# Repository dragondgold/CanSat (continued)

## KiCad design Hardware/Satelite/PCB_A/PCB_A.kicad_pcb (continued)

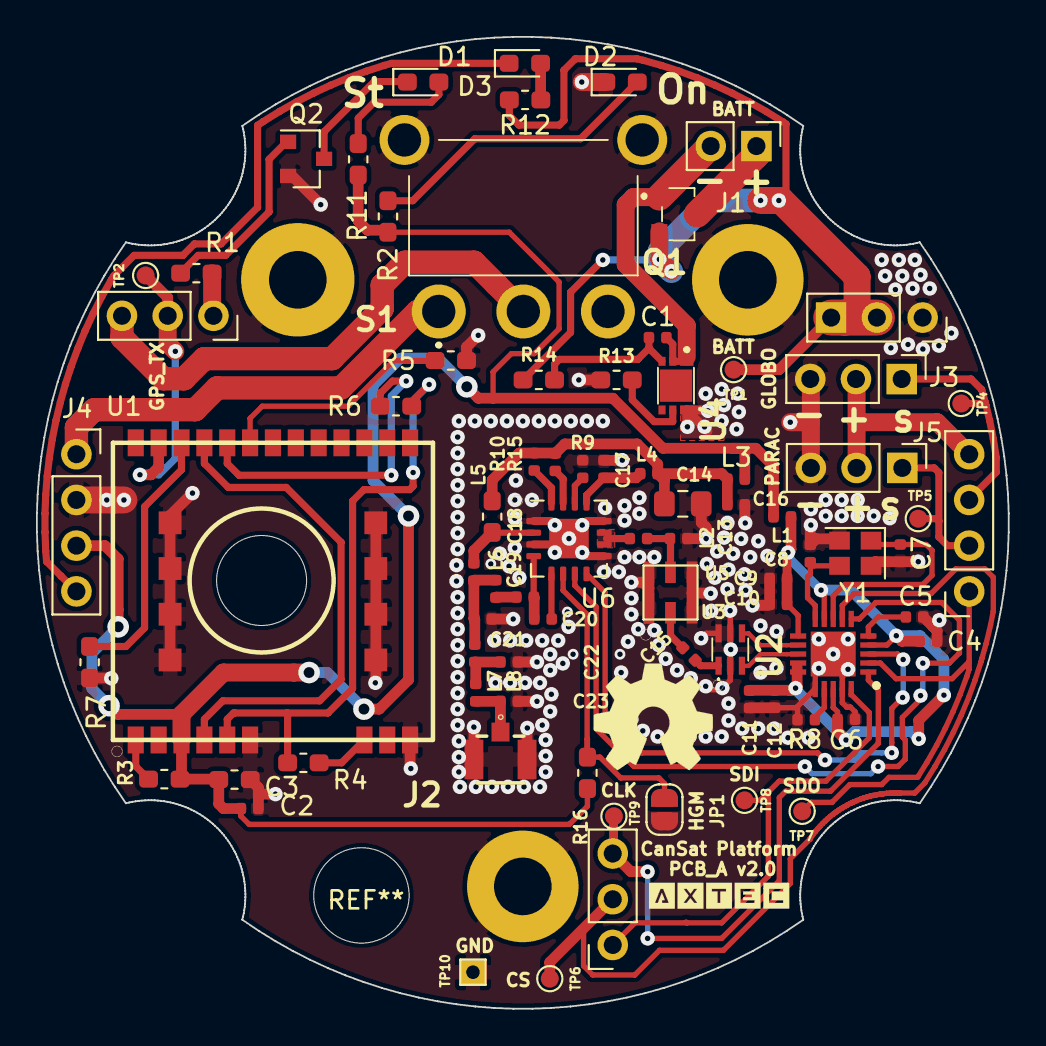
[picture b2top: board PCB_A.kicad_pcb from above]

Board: 2 copper layers, 54.0 x 54.0 mm, 79 parts (0 on the bottom side), 57 nets.

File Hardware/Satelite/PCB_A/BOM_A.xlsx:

Qty | Reference(s) | Value | Footprint | Manufacturer Part Number
9 | C1, C2, C4, C5, C6, C9, C10, C11, C12 | 100nF | Capacitor_SMD:C_0402_1005Metric | GCM155R71C104KA55D
1 | C3 | 1uF | Capacitor_SMD:C_0603_1608Metric_Pad1.05x0.95mm_HandSolder | LMK107B7105MA-T
4 | C7, C8, C16, C17 | 15pF | Capacitor_SMD:C_0402_1005Metric | C0402C150J5GACTU
1 | C13 | 0.8pF | Capacitor_SMD:C_0402_1005Metric | GRM1555C2AR80BA01D
1 | C14 | 10uF | Capacitor_SMD:C_0805_2012Metric_Pad1.15x1.40mm_HandSolder | C2012X7R1A106M125AC
1 | C15 | 100pF | Capacitor_SMD:C_0402_1005Metric | 885012005046
1 | C18 | 47pF | Capacitor_SMD:C_0402_1005Metric | GCM1555C1H470JA16J
2 | C19, C20 | 12pF | Capacitor_SMD:C_0402_1005Metric | GRM1555C1H120GA01D
1 | C21 | 3.3pF | Capacitor_SMD:C_0402_1005Metric | GJM1555C1H3R3DB01D
1 | C22 | 7.5pF | Capacitor_SMD:C_0402_1005Metric | GCM1555C1H7R5DA16D
1 | C23 | n.a | Capacitor_SMD:C_0402_1005Metric
1 | D1 | Rojo | LED_SMD:LED_0603_1608Metric_Pad1.05x0.95mm_HandSolder | 150060RS75000
2 | D2, D3 | Verde | LED_SMD:LED_0603_1608Metric_Pad1.05x0.95mm_HandSolder | 150060VS75000
1 | J1 | BaterÃ­a LiPo (Soldada) | Connector_PinHeader_2.54mm:PinHeader_1x02_P2.54mm_Vertical
1 | J2 | CONUFL001-SMD | SamacSys_Parts:CONUFL001-SMD | CONUFL001-SMD
1 | J3 | Servo Globo | Connector_PinHeader_2.54mm:PinHeader_1x03_P2.54mm_Vertical
3 | J4 | Conector_PCB_A-B | AXTEC:Conector_PCB_A-B | 22-28-5034
2 | J4 | Conector_PCB_A-B | AXTEC:Conector_PCB_A-B | 22-28-4041
1 | J5 | Servo ParacaÃ­das | Connector_PinHeader_2.54mm:PinHeader_1x03_P2.54mm_Vertical
1 | JP1 | Jumper | Jumper:SolderJumper-2_P1.3mm_Open_RoundedPad1.0x1.5mm
1 | L1 | Bead | Inductor_SMD:L_0402_1005Metric | BLM15HG102SN1D
2 | L2, L3 | 10nH | Inductor_SMD:L_0402_1005Metric | LQG15HN10NH02D
1 | L4 | 1.5nH | Inductor_SMD:L_0402_1005Metric | LQG15HS1N5S02D
1 | L5 | 22nH | Inductor_SMD:L_0603_1608Metric_Pad1.05x0.95mm_HandSolder | LQW18AN22NJ10D
1 | L6 | 7.5nH | Inductor_SMD:L_0402_1005Metric | LQW15AN7N5G00D
1 | L7 | 2.9nH | Inductor_SMD:L_0402_1005Metric | LQW15AN2N9B00D
1 | L8 | 9.1nH | Inductor_SMD:L_0402_1005Metric | LQW15AN9N1G00D
3 | M1, M2, M3 | Spacer | AXTEC:Empty_Footprint | R30-3011002
1 | MH1 | MH_CanSat | AXTEC:MH_CanSat
1 | Q1 | SSM3J338R,LF | SamacSys_Parts:SSM3J332RLFT | SSM3J338R,LF
1 | Q2 | BC817 | Package_TO_SOT_SMD:SOT-23 | BC817-16LT1G
4 | R1, R2, R11, R12 | 1k | Resistor_SMD:R_0603_1608Metric_Pad1.05x0.95mm_HandSolder | RC0603JR-071KL
5 | R3, R4, R5, R6, R7 | 10k | Resistor_SMD:R_0603_1608Metric_Pad1.05x0.95mm_HandSolder | RC0603JR-0710KL
1 | R8 | 56k | Resistor_SMD:R_0402_1005Metric | RC0402FR-0756KL
1 | R9 | 3.3k | Resistor_SMD:R_0402_1005Metric | RC0402FR-073K3L
1 | R10 | 10R | Resistor_SMD:R_0402_1005Metric | RC0402FR-0710RL
1 | R13 | 2.7k | Resistor_SMD:R_0603_1608Metric_Pad1.05x0.95mm_HandSolder | RC0603FR-072K7L
1 | R14 | 330 | Resistor_SMD:R_0603_1608Metric_Pad1.05x0.95mm_HandSolder | RC0603FR-07330RL
1 | R15 | 47R | Resistor_SMD:R_0402_1005Metric | RC0402FR-0747RL
1 | R16 | 10K | Resistor_SMD:R_0603_1608Metric_Pad1.05x0.95mm_HandSolder | RC0603JR-0710KL
1 | S1 | 500SSP1S1M6QEA | SamacSys_Parts:500SSP1S1M6QEA | 500SSP1S1M6QEA
1 | U1 | A2235-H | AXTEC:A2235-H | A2235-H
1 | U2 | CC1101RGP | SamacSys_Parts:QFN50P400X400X100-21N-D | CC1101RGP
1 | U3 | 0915BM15A0001E | SamacSys_Parts:0915BM15A0001E | 0915BM15A0001E
1 | U4 | AP9211SA-AF-HAC-7 | SamacSys_Parts:AP9211SAACHAC7 | AP9211SA-AF-HAC-7
1 | U5 | B39921B3588U410 | AXTEC:B39921B3588U410 | B39921B3588U410
1 | U6 | CC1190 | Package_DFN_QFN:Texas_S-PVQFN-N16_EP2.7x2.7mm | CC1190RGVR
1 | Y1 | 26 MHz | Crystal:Crystal_SMD_2520-4Pin_2.5x2.0mm | FA-20H 26.0000MF12V-W
1 |  | Antena 915 MHz |  | W3312B0100

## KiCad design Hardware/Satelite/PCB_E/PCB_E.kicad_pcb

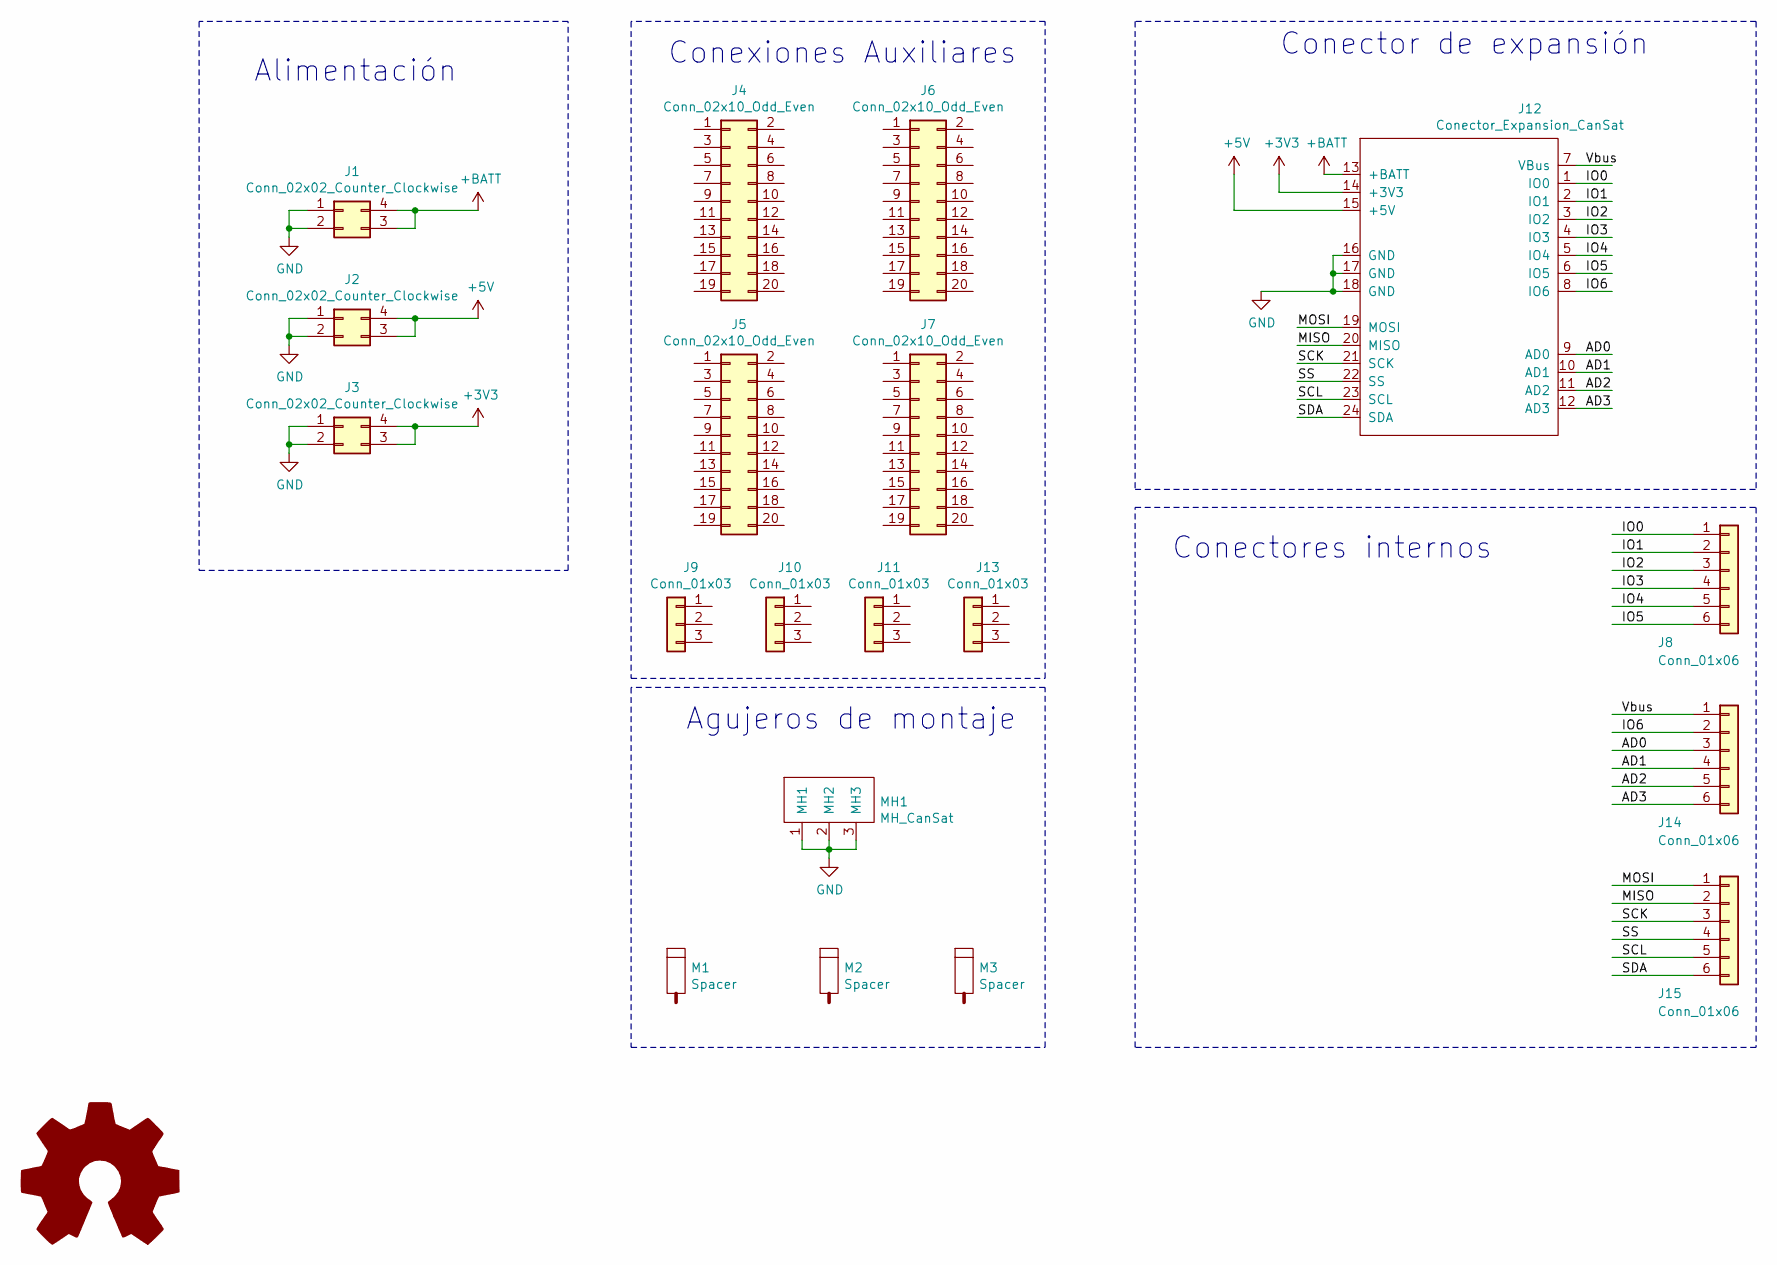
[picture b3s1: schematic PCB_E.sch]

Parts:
J1, J2, J3: Conn_02x02_Counter_Clockwise; PinSocket_2x02_P2.54mm_Vertical
J4, J5, J6, J7: Conn_02x10_Odd_Even; PinSocket_2x10_P2.54mm_Vertical
J8, J14, J15: Conn_01x06; PinHeader_1x06_P2.54mm_Vertical
J9, J10, J11, J13: Conn_01x03; PinHeader_1x03_P2.54mm_Vertical
J12: Conector_Expansion_CanSat
M1, M2, M3: Spacer; Empty_Footprint; Manufacturer Part Number R30-3011202
MH1: MH_CanSat

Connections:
+3V3: J3.3, J3.4, J12.14 (+3V3)
+5V: J2.3, J2.4, J12.15 (+5V)
+BATT: J1.3, J1.4, J12.13 (+BATT)
/AD0: J12.9 (AD0), J14.3
/AD1: J12.10 (AD1), J14.4
/AD2: J12.11 (AD2), J14.5
/AD3: J12.12 (AD3), J14.6
/IO0: J8.1, J12.1 (IO0)
/IO1: J8.2, J12.2 (IO1)
/IO2: J8.3, J12.3 (IO2)
/IO3: J8.4, J12.4 (IO3)
/IO4: J8.5, J12.5 (IO4)
/IO5: J8.6, J12.6 (IO5)
/IO6: J12.8 (IO6), J14.2
/MISO: J12.20 (MISO), J15.2
/MOSI: J12.19 (MOSI), J15.1
/SCK: J12.21 (SCK), J15.3
/SCL: J12.23 (SCL), J15.5
/SDA: J12.24 (SDA), J15.6
/SS: J12.22 (SS), J15.4
/Vbus: J12.7 (VBus), J14.1
GND: J1.1, J1.2, J2.1, J2.2, J3.1, J3.2, J12.16 (GND), J12.17 (GND), J12.18 (GND), MH1.1 (MH1), MH1.2 (MH2), MH1.3 (MH3)

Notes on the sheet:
Conexiones Auxiliares
Alimentación
Conectores internos
Conector de expansión
Agujeros de montaje

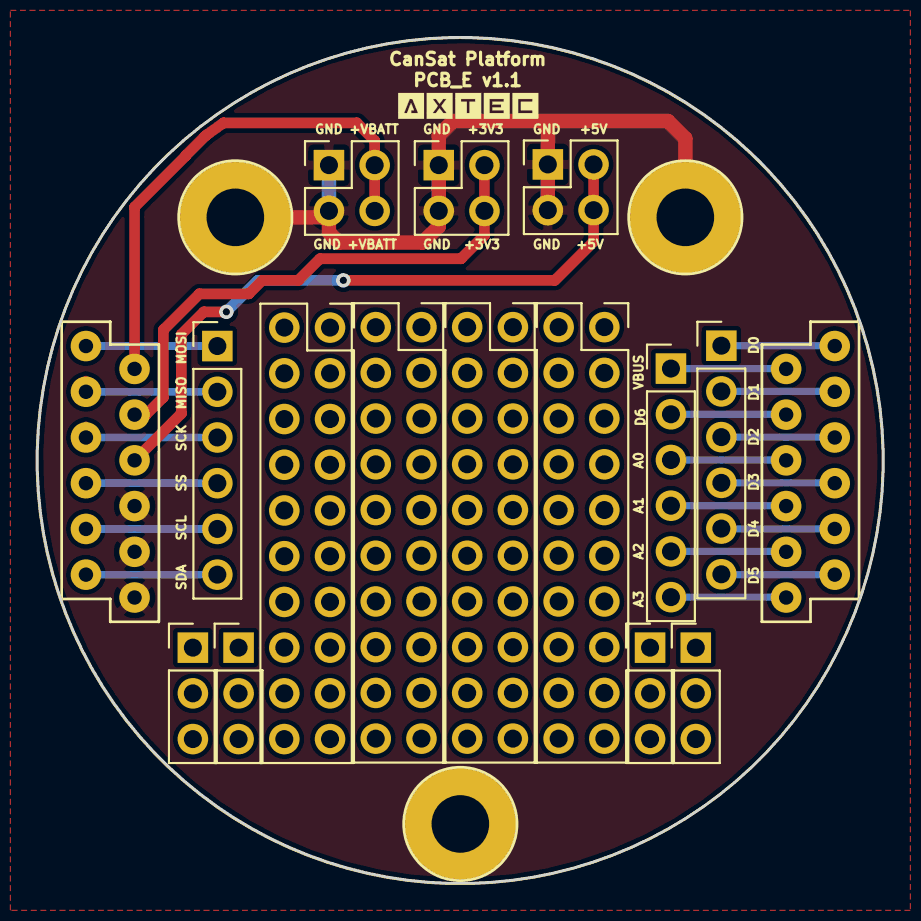
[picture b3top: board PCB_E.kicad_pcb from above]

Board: 2 copper layers, 47.0 x 47.0 mm, 19 parts (0 on the bottom side), 22 nets.

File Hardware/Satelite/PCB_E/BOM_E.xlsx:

Qty | Reference(s) | Value | Footprint | Manufacturer Part Number
3 | J1, J2, J3 | Conn_02x02_Counter_Clockwise | Connector_PinSocket_2.54mm:PinSocket_2x02_P2.54mm_Vertical
4 | J4, J5, J6, J7 | Conn_02x10_Odd_Even | Connector_PinSocket_2.54mm:PinSocket_2x10_P2.54mm_Vertical
3 | J8, J14, J15 | Conn_01x06 | Connector_PinHeader_2.54mm:PinHeader_1x06_P2.54mm_Vertical
4 | J9, J10, J11, J13 | Conn_01x03 | Connector_PinHeader_2.54mm:PinHeader_1x03_P2.54mm_Vertical
4 | J12 | Conector_Expansion_CanSat | AXTEC:Conector_Expansion_CanSat | SSQ-106-03-T-S
3 | M1, M2, M3 | Spacer | AXTEC:Empty_Footprint | R30-3011202
1 | MH1 | MH_CanSat | AXTEC:MH_CanSat

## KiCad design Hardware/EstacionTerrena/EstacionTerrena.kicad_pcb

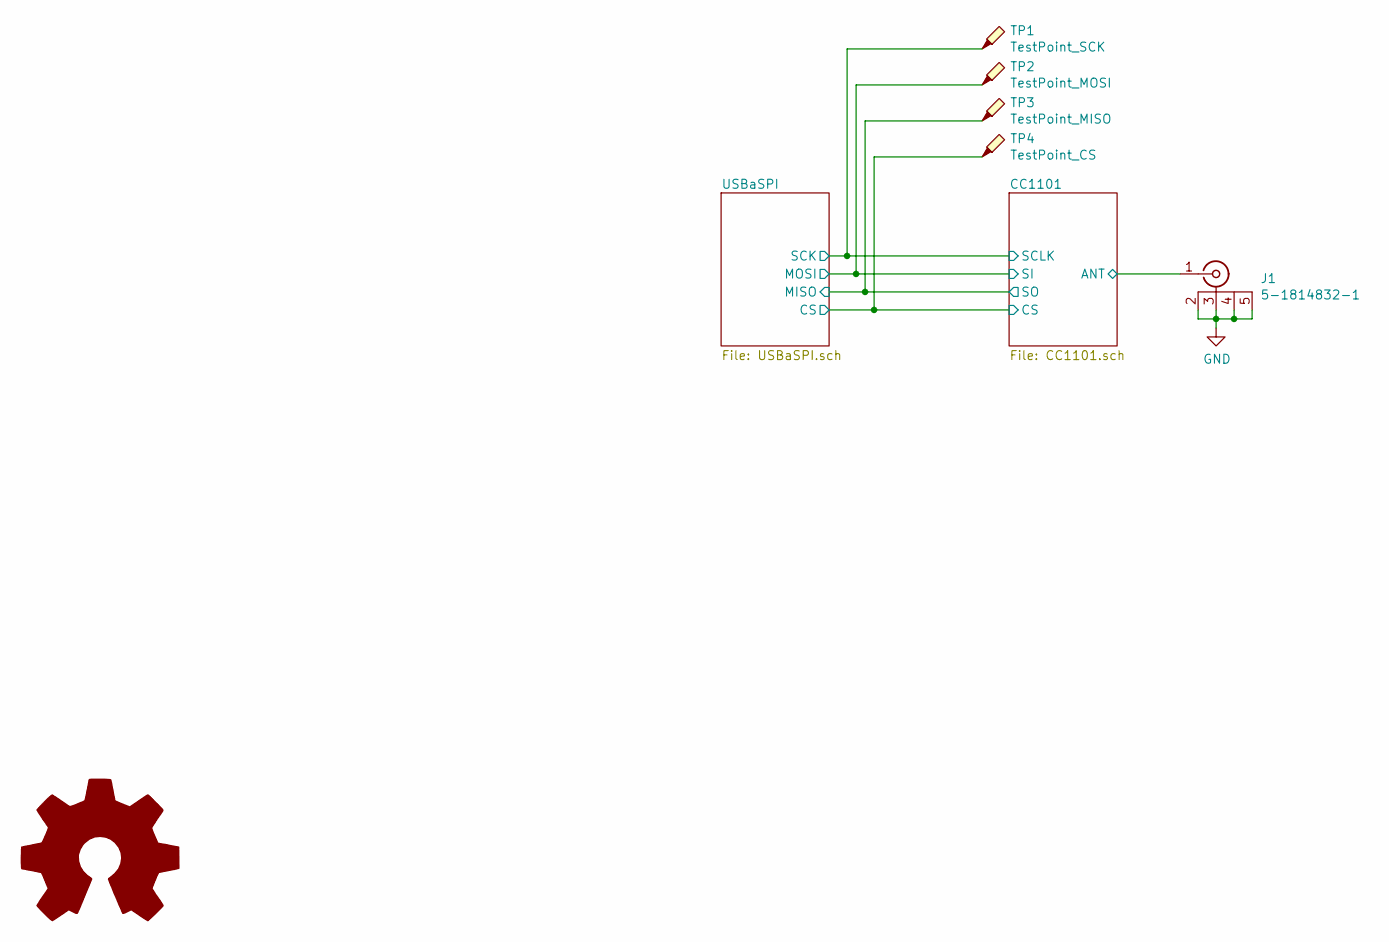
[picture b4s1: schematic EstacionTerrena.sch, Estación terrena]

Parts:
J1: 5-1814832-1; Manufacturer Part Number 5-1814832-1
TP1: TestPoint_SCK; TestPoint_Pad_D1.0mm
TP2: TestPoint_MOSI; TestPoint_Pad_D1.0mm
TP3: TestPoint_MISO; TestPoint_Pad_D1.0mm
TP4: TestPoint_CS; TestPoint_Pad_D1.0mm

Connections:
/CC1101/ANT: J1.1; also elsewhere on the board
/CC1101/CS: TP4.1; also elsewhere on the board
/USBaSPI/MISO: TP3.1; also elsewhere on the board
/USBaSPI/MOSI: TP2.1; also elsewhere on the board
/USBaSPI/SCK: TP1.1; also elsewhere on the board
GND: J1.2, J1.3, J1.4, J1.5; also elsewhere on the board

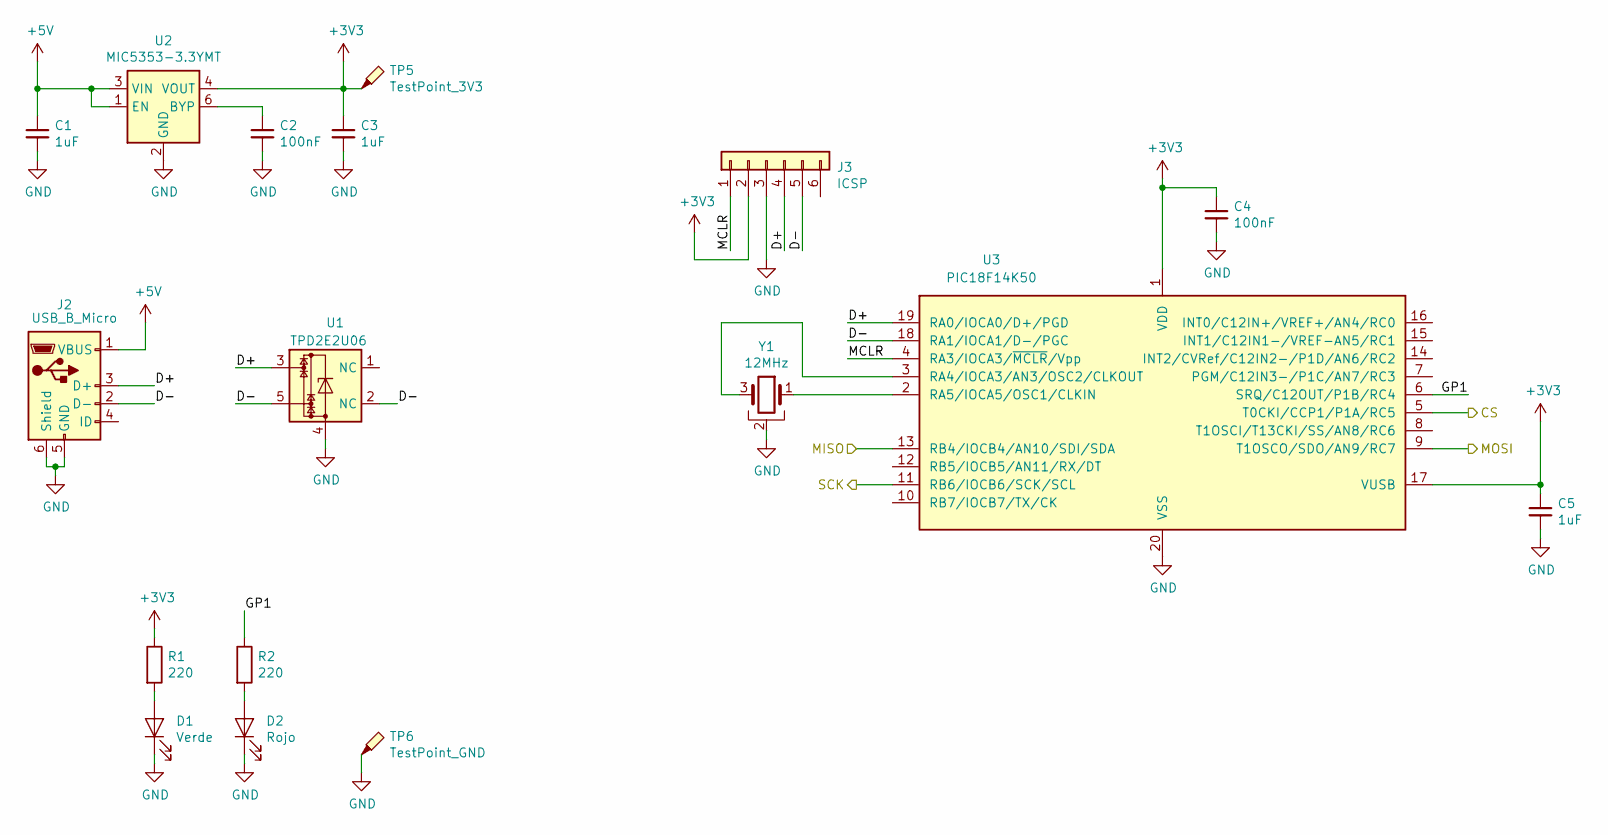
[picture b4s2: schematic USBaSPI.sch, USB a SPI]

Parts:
C1, C3, C5: 1uF; C_0603_1608Metric; Voltage 10V; Manufacturer Part Number LMK107B7105MA-T
C2, C4: 100nF; C_0603_1608Metric; Voltage 16V; Manufacturer Part Number EMK107B7104KAHT
D1: Verde; LED_0603_1608Metric; Manufacturer Part Number 150060VS75000
D2: Rojo; LED_0603_1608Metric; Manufacturer Part Number 150060RS75000
J2: USB_B_Micro; USB_Micro-B_Molex_47346-0001; Manufacturer Part Number 47346-1001
J3: ICSP; PinHeader_1x06_P2.54mm_Vertical
R1, R2: 220; R_0603_1608Metric_Pad1.05x0.95mm_HandSolder; Manufacturer Part Number RC0603JR-13220RL
TP5: TestPoint_3V3; TestPoint_Pad_D1.0mm
TP6: TestPoint_GND; TestPoint_THTPad_1.0x1.0mm_Drill0.5mm
U1: TPD2E2U06; SOT-553; Manufacturer Part Number TPD2E2U06DRLR
U2: MIC5353-3.3YMT; MLF-6-1EP_1.6x1.6mm_P0.5mm_EP0.5x1.26mm; Manufacturer Part Number MIC5353-3.3YMT-TR
U3: PIC18F14K50; SSOP-20_5.3x7.2mm_P0.65mm; Manufacturer Part Number PIC18F14K50-I/SS
Y1: 12MHz; Resonator_SMD_muRata_CSTxExxV-3Pin_3.0x1.1mm; Manufacturer Part Number CSTNE12M0GH5L000R0

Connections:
+3V3: C3.1, C4.1, C5.1, J3.2, R1.1, TP5.1, U2.4 (VOUT), U3.1 (VDD), U3.17 (VUSB); also elsewhere on the board
+5V: C1.1, J2.1 (VBUS), U2.1 (EN), U2.3 (VIN)
/CC1101/CS: U3.5 (T0CKI/CCP1/P1A/RC5); also elsewhere on the board
/USBaSPI/D+: J2.3 (D+), J3.4, U1.3, U3.19 (RA0/IOCA0/D+/PGD)
/USBaSPI/D-: J2.2 (D-), J3.5, U1.2 (NC), U1.5, U3.18 (RA1/IOCA1/D-/PGC)
/USBaSPI/GP1: R2.1, U3.6 (SRQ/C12OUT/P1B/RC4)
/USBaSPI/MCLR: J3.1, U3.4 (RA3/IOCA3/~MCLR~/Vpp)
/USBaSPI/MISO: U3.13 (RB4/IOCB4/AN10/SDI/SDA); also elsewhere on the board
/USBaSPI/MOSI: U3.9 (T1OSCO/SDO/AN9/RC7); also elsewhere on the board
/USBaSPI/SCK: U3.11 (RB6/IOCB6/SCK/SCL); also elsewhere on the board
GND: C1.2, C2.2, C3.2, C4.2, C5.2, D1.1 (K), D2.1 (K), J2.5 (GND), J2.6 (Shield), J3.3, TP6.1, U1.4, U2.2 (GND), U2.7 (GND), U3.20 (VSS), Y1.2; also elsewhere on the board
unnamed: C2.1, U2.6 (BYP)
unnamed: D1.2 (A), R1.2
unnamed: D2.2 (A), R2.2
unnamed: U3.2 (RA5/IOCA5/OSC1/CLKIN), Y1.1
unnamed: U3.3 (RA4/IOCA3/AN3/OSC2/CLKOUT), Y1.3

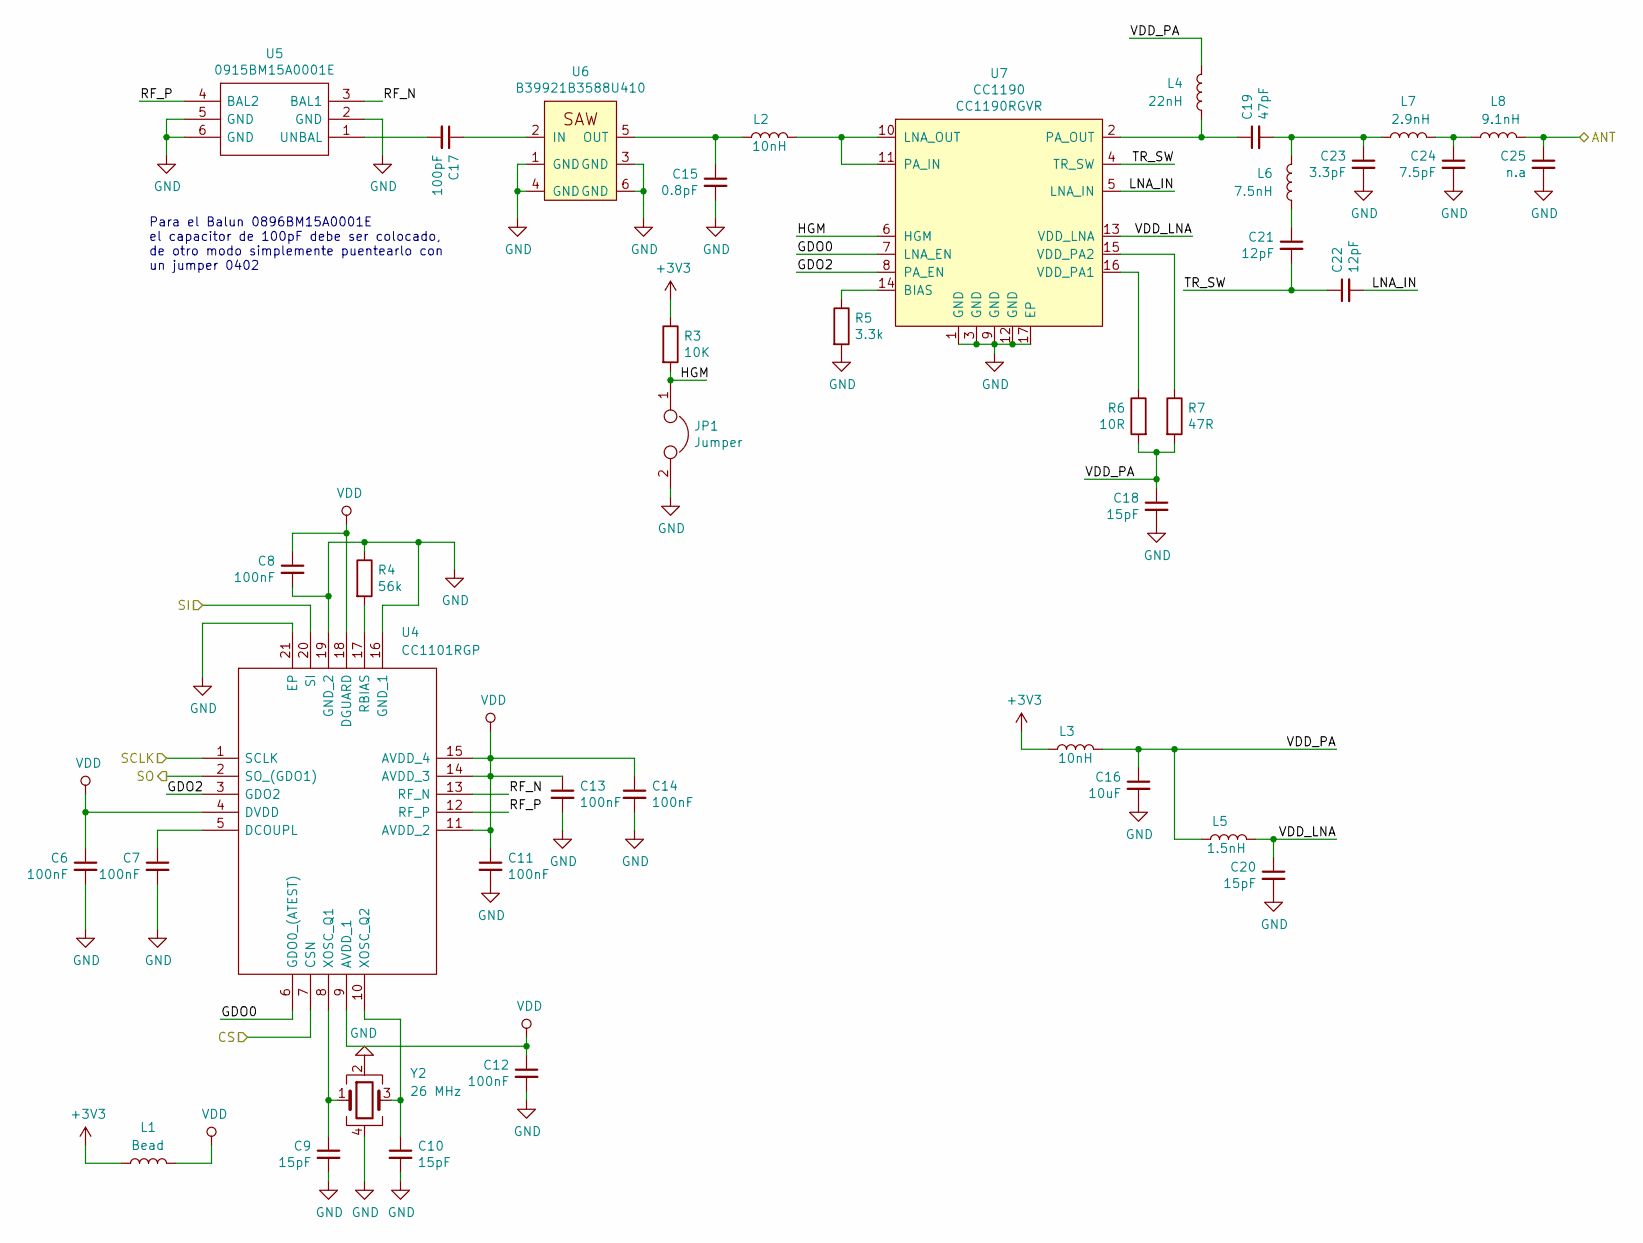
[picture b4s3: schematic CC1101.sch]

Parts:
C6, C7, C8, C11, C12, C13, C14: 100nF; C_0402_1005Metric; Voltage 16V; Manufacturer Part Number GCM155R71C104KA55D
C9, C10: 15pF; C_0402_1005Metric; Voltage 10V; Manufacturer Part Number C0402C150J5GACTU
C15: 0.8pF; C_0402_1005Metric; Manufacturer Part Number GRM1555C2AR80BA01D
C16: 10uF; C_0805_2012Metric_Pad1.15x1.40mm_HandSolder; Manufacturer Part Number C2012X7R1A106M125AC
C17: 100pF; C_0402_1005Metric; Voltage 25V; Manufacturer Part Number 885012005046
C18, C20: 15pF; C_0402_1005Metric; Manufacturer Part Number CC0402JRNPO9BN150
C19: 47pF; C_0402_1005Metric; Manufacturer Part Number GCM1555C1H470JA16J
C21, C22: 12pF; C_0402_1005Metric; Manufacturer Part Number GRM1555C1H120GA01D
C23: 3.3pF; C_0402_1005Metric; Manufacturer Part Number GJM1555C1H3R3DB01D
C24: 7.5pF; C_0402_1005Metric; Manufacturer Part Number GCM1555C1H7R5DA16D
C25: n.a; C_0402_1005Metric
JP1: Jumper; SolderJumper-2_P1.3mm_Open_RoundedPad1.0x1.5mm
L1: Bead; L_0402_1005Metric; Manufacturer Part Number BLM15HG102SN1D
L2, L3: 10nH; L_0402_1005Metric; Manufacturer Part Number LQG15HN10NH02D
L4: 22nH; L_0603_1608Metric_Pad1.05x0.95mm_HandSolder; Manufacturer Part Number LQW18AN22NJ10D
L5: 1.5nH; L_0402_1005Metric; Manufacturer Part Number LQG15HS1N5S02D
L6: 7.5nH; L_0402_1005Metric; Manufacturer Part Number LQW15AN7N5G00D
L7: 2.9nH; L_0402_1005Metric; Manufacturer Part Number LQW15AN2N9B00D
L8: 9.1nH; L_0402_1005Metric; Manufacturer Part Number LQW15AN9N1G00D
R3: 10K; R_0603_1608Metric_Pad1.05x0.95mm_HandSolder; Manufacturer Part Number RC0603JR-0710KL
R4: 56k; R_0402_1005Metric; Manufacturer Part Number RC0402FR-0756KL
R5: 3.3k; R_0402_1005Metric; Manufacturer Part Number RC0402FR-073K3L
R6: 10R; R_0402_1005Metric; Manufacturer Part Number RC0402FR-0710RL
R7: 47R; R_0402_1005Metric; Manufacturer Part Number RC0402FR-0747RL
U4: CC1101RGP; QFN-20-1EP_4x4mm_P0.5mm_EP2.5x2.5mm; Manufacturer Part Number CC1101RGP
U5: 0915BM15A0001E; Manufacturer Part Number 0915BM15A0001E
U6: B39921B3588U410; Manufacturer Part Number B39921B3588U410
U7: CC1190; Texas_S-PVQFN-N16_EP2.7x2.7mm; Manufactuer Part Number CC1190RGVR
Y2: 26 MHz; Crystal_SMD_2520-4Pin_2.5x2.0mm; Manufacturer Part Number FA-20H 26.0000MF12V-W

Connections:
+3V3: L1.2, L3.1, R3.1; also elsewhere on the board
/CC1101/ANT: C25.1, L8.1; also elsewhere on the board
/CC1101/CS: U4.7 (CSN); also elsewhere on the board
/CC1101/GDO0: U4.6 (GDO0_(ATEST)), U7.7 (LNA_EN)
/CC1101/GDO2: U4.3 (GDO2), U7.8 (PA_EN)
/CC1101/HGM: JP1.1, R3.2, U7.6 (HGM)
/CC1101/LNA_IN: C22.2, U7.5 (LNA_IN)
/CC1101/RF_N: U4.13 (RF_N), U5.3 (BAL1)
/CC1101/RF_P: U4.12 (RF_P), U5.4 (BAL2)
/CC1101/TR_SW: C21.2, C22.1, U7.4 (TR_SW)
/CC1101/VDD_LNA: C20.1, L5.2, U7.13 (VDD_LNA)
/CC1101/VDD_PA: C16.1, C18.1, L3.2, L4.1, L5.1, R6.2, R7.2
/USBaSPI/MISO: U4.2 (SO_(GDO1)); also elsewhere on the board
/USBaSPI/MOSI: U4.20 (SI); also elsewhere on the board
/USBaSPI/SCK: U4.1 (SCLK); also elsewhere on the board
GND: C6.2, C7.2, C8.2, C9.2, C10.2, C11.2, C12.2, C13.2, C14.2, C15.2, C16.2, C18.2, C20.2, C23.2, C24.2, C25.2, JP1.2, R4.1, R5.2, U4.16 (GND_1), U4.19 (GND_2), U4.21 (EP), U5.2 (GND), U5.5 (GND), U5.6 (GND), U6.1 (GND), U6.3 (GND), U6.4 (GND), U6.6 (GND), U7.1 (GND), U7.3 (GND), U7.9 (GND), U7.12 (GND), U7.17 (EP), Y2.2, Y2.4; also elsewhere on the board
unnamed: C7.1, U4.5 (DCOUPL)
unnamed: C9.1, U4.8 (XOSC_Q1), Y2.1
unnamed: C10.1, U4.10 (XOSC_Q2), Y2.3
unnamed: C15.1, L2.1, U6.5 (OUT)
unnamed: C17.1, U6.2 (IN)
unnamed: C17.2, U5.1 (UNBAL)
unnamed: C19.1, L4.2, U7.2 (PA_OUT)
unnamed: C19.2, C23.1, L6.1, L7.2
unnamed: C21.1, L6.2
unnamed: C24.1, L7.1, L8.2
unnamed: L2.2, U7.10 (LNA_OUT), U7.11 (PA_IN)
unnamed: R4.2, U4.17 (RBIAS)
unnamed: R5.1, U7.14 (BIAS)
unnamed: R6.1, U7.16 (VDD_PA1)
unnamed: R7.1, U7.15 (VDD_PA2)
VDD: C6.1, C8.1, C11.1, C12.1, C13.1, C14.1, L1.1, U4.4 (DVDD), U4.9 (AVDD_1), U4.11 (AVDD_2), U4.14 (AVDD_3), U4.15 (AVDD_4), U4.18 (DGUARD)

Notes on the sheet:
Para el Balun 0896BM15A0001E el capacitor de 100pF debe ser colocado, de otro modo simplemente puentearlo con un jumper 0402

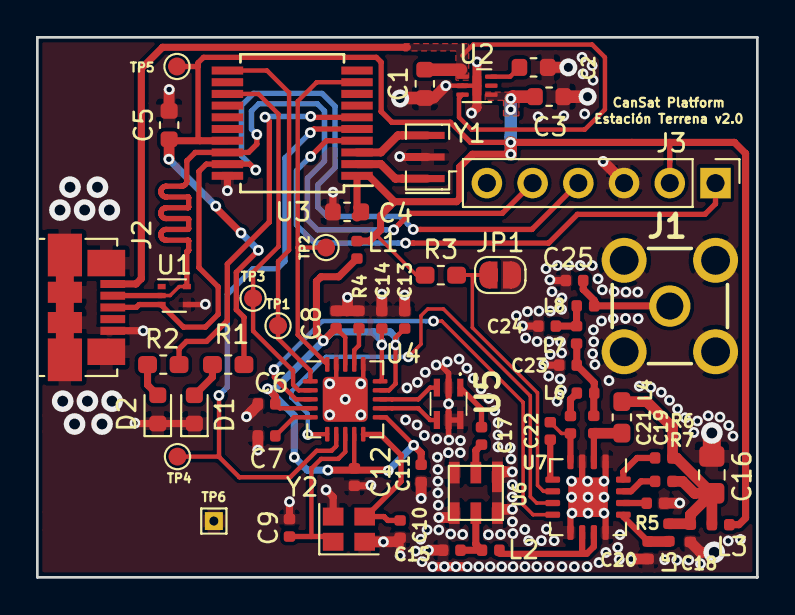
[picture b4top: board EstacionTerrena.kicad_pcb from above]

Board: 2 copper layers, 40.0 x 30.0 mm, 61 parts (0 on the bottom side), 42 nets.

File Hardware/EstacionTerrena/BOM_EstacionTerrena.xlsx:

Qty | Reference(s) | Value | Footprint | Manufacturer Part Number
3 | C1, C3, C5 | 1uF | Capacitor_SMD:C_0603_1608Metric | LMK107B7105MA-T
2 | C2, C4 | 100nF | Capacitor_SMD:C_0603_1608Metric | EMK107B7104KAHT
7 | C6, C7, C8, C11, C12, C13, C14 | 100nF | Capacitor_SMD:C_0402_1005Metric | GCM155R71C104KA55D
4 | C9, C10, C18, C20 | 15pF | Capacitor_SMD:C_0402_1005Metric | C0402C150J5GACTU
1 | C15 | 0.8pF | Capacitor_SMD:C_0402_1005Metric | GRM1555C2AR80BA01D
1 | C16 | 10uF | Capacitor_SMD:C_0805_2012Metric_Pad1.15x1.40mm_HandSolder | C2012X7R1A106M125AC
1 | C17 | 100pF | Capacitor_SMD:C_0402_1005Metric | 885012005046
1 | C19 | 47pF | Capacitor_SMD:C_0402_1005Metric | GCM1555C1H470JA16J
2 | C21, C22 | 12pF | Capacitor_SMD:C_0402_1005Metric | GRM1555C1H120GA01D
1 | C23 | 3.3pF | Capacitor_SMD:C_0402_1005Metric | GJM1555C1H3R3DB01D
1 | C24 | 7.5pF | Capacitor_SMD:C_0402_1005Metric | GCM1555C1H7R5DA16D
1 | C25 | n.a | Capacitor_SMD:C_0402_1005Metric
1 | D1 | Verde | LED_SMD:LED_0603_1608Metric | 150060VS75000
1 | D2 | Rojo | LED_SMD:LED_0603_1608Metric | 150060RS75000
1 | J1 | 5-1814832-1 | SamacSys_Parts:5-1814832-1 | 5-1814832-1
1 | J2 | USB_B_Micro | Connector_USB:USB_Micro-B_Molex_47346-0001 | 47346-1001
1 | J3 | ICSP | Connector_PinHeader_2.54mm:PinHeader_1x06_P2.54mm_Vertical
1 | JP1 | Jumper | Jumper:SolderJumper-2_P1.3mm_Open_RoundedPad1.0x1.5mm
1 | L1 | Bead | Inductor_SMD:L_0402_1005Metric | BLM15HG102SN1D
2 | L2, L3 | 10nH | Inductor_SMD:L_0402_1005Metric | LQG15HN10NH02D
1 | L4 | 22nH | Inductor_SMD:L_0603_1608Metric_Pad1.05x0.95mm_HandSolder | LQW18AN22NJ10D
1 | L5 | 1.5nH | Inductor_SMD:L_0402_1005Metric | LQG15HS1N5S02D
1 | L6 | 7.5nH | Inductor_SMD:L_0402_1005Metric | LQW15AN7N5G00D
1 | L7 | 2.9nH | Inductor_SMD:L_0402_1005Metric | LQW15AN2N9B00D
1 | L8 | 9.1nH | Inductor_SMD:L_0402_1005Metric | LQW15AN9N1G00D
2 | R1, R2 | 220 | Resistor_SMD:R_0603_1608Metric_Pad1.05x0.95mm_HandSolder | RC0603JR-13220RL
1 | R3 | 10K | Resistor_SMD:R_0603_1608Metric_Pad1.05x0.95mm_HandSolder | RC0603JR-0710KL
1 | R4 | 56k | Resistor_SMD:R_0402_1005Metric | RC0402FR-0756KL
1 | R5 | 3.3k | Resistor_SMD:R_0402_1005Metric | RC0402FR-073K3L
1 | R6 | 10R | Resistor_SMD:R_0402_1005Metric | RC0402FR-0710RL
1 | R7 | 47R | Resistor_SMD:R_0402_1005Metric | RC0402FR-0747RL
1 | U1 | TPD2E2U06 | Package_TO_SOT_SMD:SOT-553 | TPD2E2U06DRLR
1 | U2 | MIC5353-3.3YMT | Package_DFN_QFN:MLF-6-1EP_1.6x1.6mm_P0.5mm_EP0.5x1.26mm | MIC5353-3.3YMT-TR
1 | U3 | PIC18F14K50 | Package_SO:SSOP-20_5.3x7.2mm_P0.65mm | PIC18F14K50-I/SS
1 | U4 | CC1101RGP | Package_DFN_QFN:QFN-20-1EP_4x4mm_P0.5mm_EP2.5x2.5mm | CC1101RGP
1 | U5 | 0915BM15A0001E | SamacSys_Parts:0915BM15A0001E | 0915BM15A0001E
1 | U6 | B39921B3588U410 | AXTEC:B39921B3588U410 | B39921B3588U410
1 | U7 | CC1190 | Package_DFN_QFN:Texas_S-PVQFN-N16_EP2.7x2.7mm | CC1190RGVR
1 | Y1 | 12MHz | Crystal:Resonator_SMD_muRata_CSTxExxV-3Pin_3.0x1.1mm | CSTNE12M0GH5L000R0
1 | Y2 | 26 MHz | Crystal:Crystal_SMD_2520-4Pin_2.5x2.0mm | FA-20H 26.0000MF12V-W
